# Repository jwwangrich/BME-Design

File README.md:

# BME-Design

BME790-03

This is for the LED Lighting Project made by Rich Wang

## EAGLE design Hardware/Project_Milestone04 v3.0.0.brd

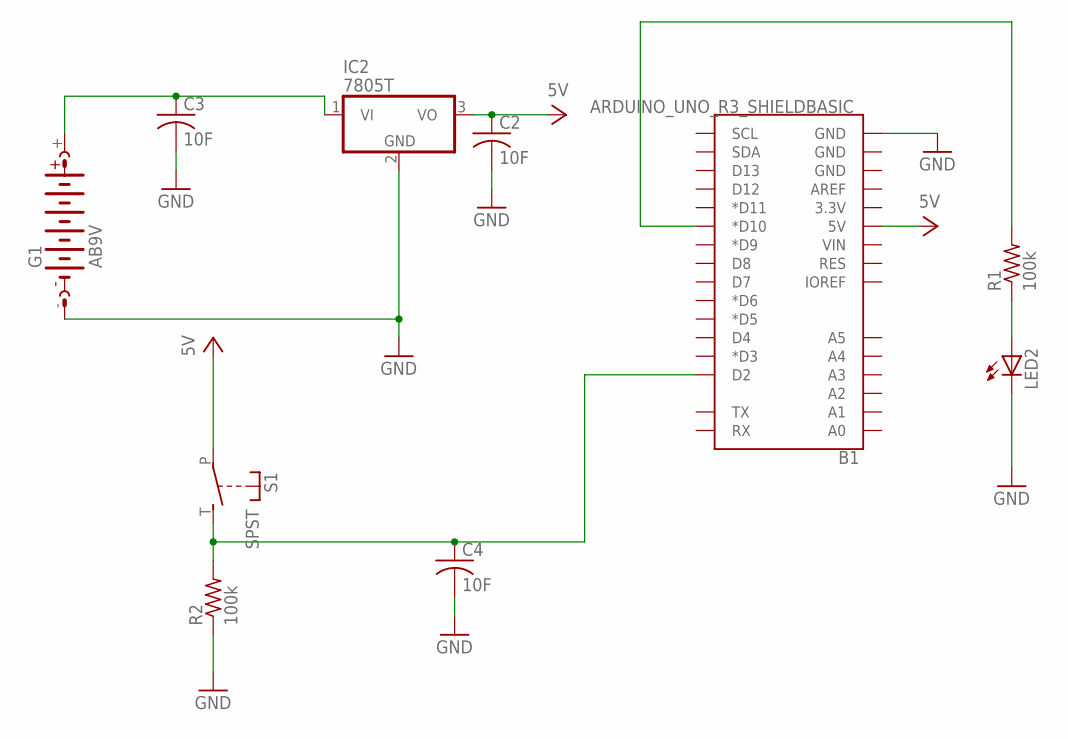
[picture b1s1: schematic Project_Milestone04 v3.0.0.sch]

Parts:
B1: ARDUINO_UNO_R3_SHIELDBASIC; UNO_R3_SHIELD
C2, C3, C4: 10F; C0805
G1: AB9V
IC2: 7805T; TO220H
LED2: LED5MM
R1, R2: 100k; 0207/10
S1: SPST; JUDCOSPST

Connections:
GND: B1.GND@0 (GND), C2.2, C3.2, C4.2, G1.-, IC2.2 (GND), LED2.K (C), R2.1
unnamed: C3.1, G1.+, IC2.1 (VI)
unnamed: B1.D10 (*D10), R1.2
unnamed: LED2.A, R1.1
unnamed: B1.D2, C4.1, R2.2, S1.T (S)
VCC: B1.5V, C2.1, IC2.3 (VO), S1.P

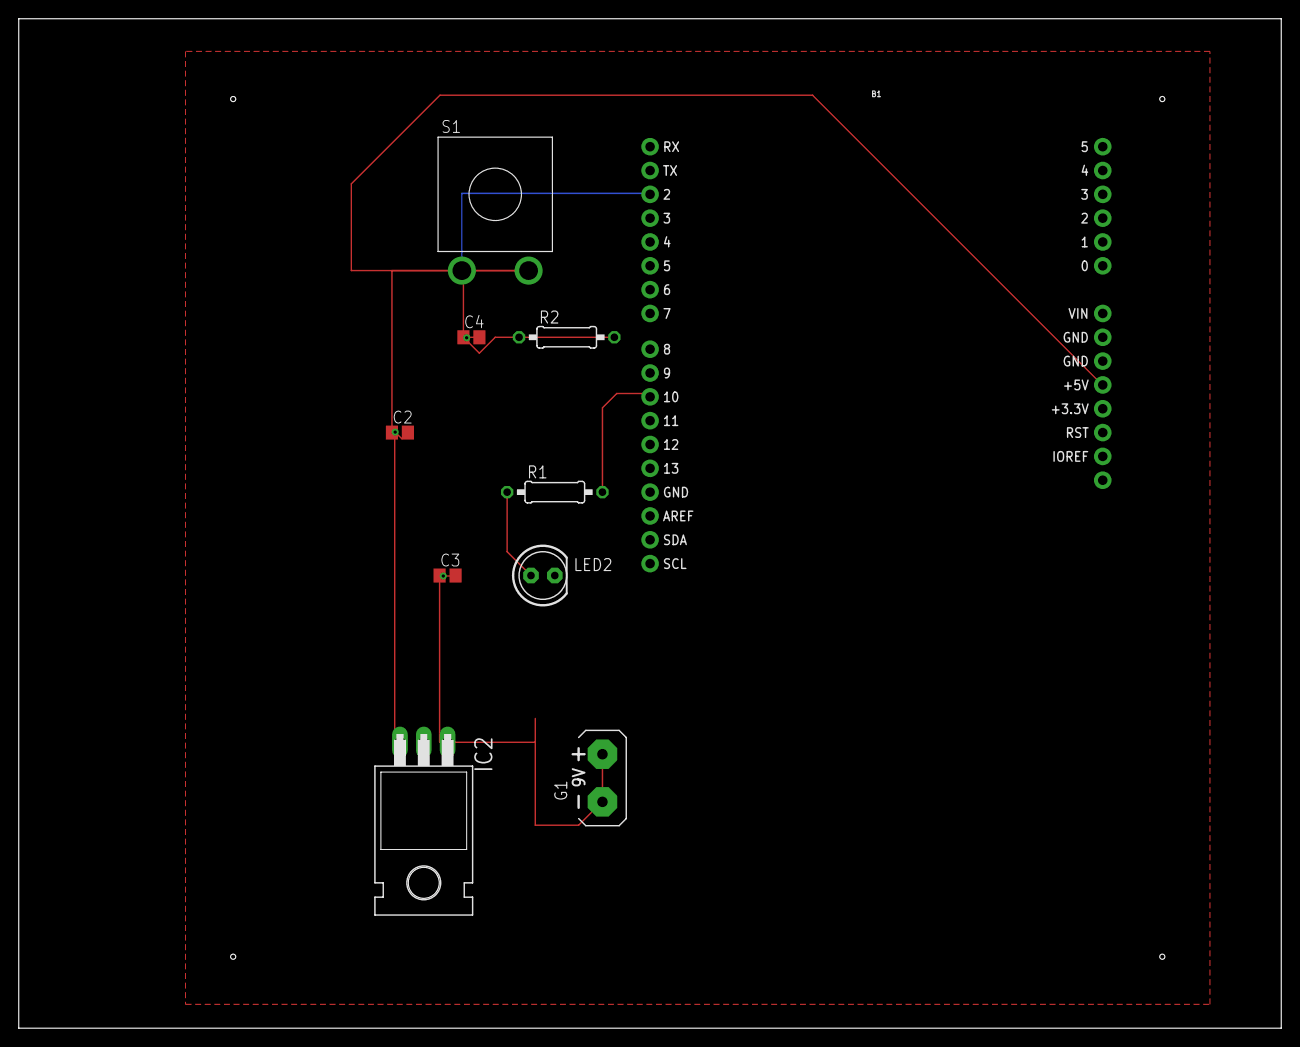
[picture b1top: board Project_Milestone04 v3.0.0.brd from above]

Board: 2 copper layers, 134.6 x 107.6 mm, 10 parts (0 on the bottom side), 6 nets.

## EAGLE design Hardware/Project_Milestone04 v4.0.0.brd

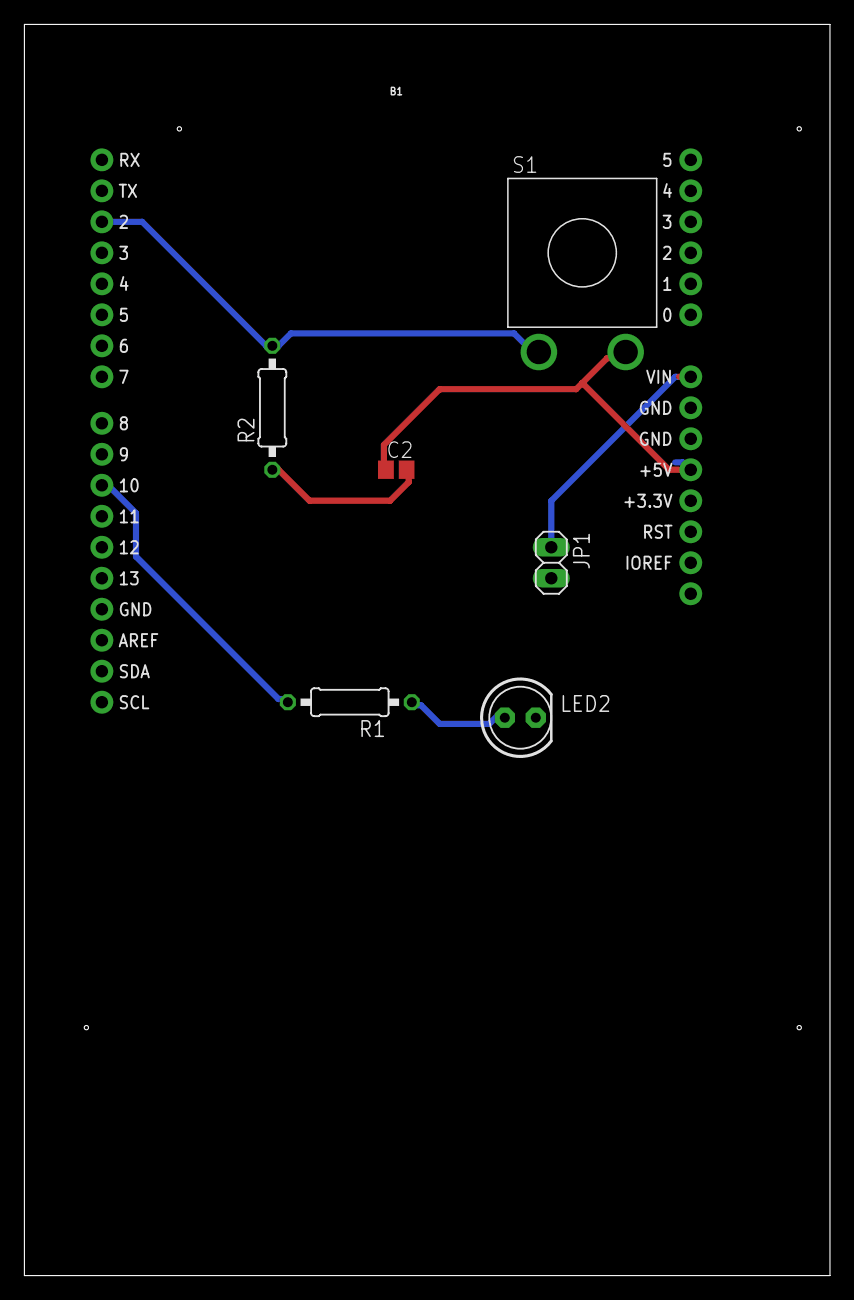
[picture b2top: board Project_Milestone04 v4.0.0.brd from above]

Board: 2 copper layers, 66.0 x 102.5 mm, 7 parts (0 on the bottom side), 6 nets.

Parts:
B1: ARDUINO_UNO_R3_SHIELDBASIC; UNO_R3_SHIELD
C2: 10F; C0805
JP1: 1X02
LED2: LED5MM
R1, R2: 100k; 0207/10
S1: SPST; JUDCOSPST

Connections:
GND: B1.GND@0, C2.2, JP1.2, LED2.K, R2.1
unnamed: B1.VIN, JP1.1
unnamed: B1.D10, R1.2
unnamed: LED2.A, R1.1
unnamed: B1.D2, R2.2, S1.T
VCC: B1.5V, C2.1, S1.P

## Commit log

2018-10-01 mkdir
2018-11-08 project
2018-11-08 add ECAD csh and pcb files
2018-11-21 CAD project with updated PCB board
2018-12-02 pcb updated
2018-12-03 pcb version v4.0.0
2018-12-04 update pcb schematic with holes
2018-12-06 working software
2018-12-13 project updated version2.0.0 on 12/13/2018
2018-12-14 final version LED project

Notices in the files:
parts and their libraries:
SparkFun-Boards: Licensing: Creative Commons ShareAlike 4.0 International - https://creativecommons.org/licenses/by-sa/4.0
